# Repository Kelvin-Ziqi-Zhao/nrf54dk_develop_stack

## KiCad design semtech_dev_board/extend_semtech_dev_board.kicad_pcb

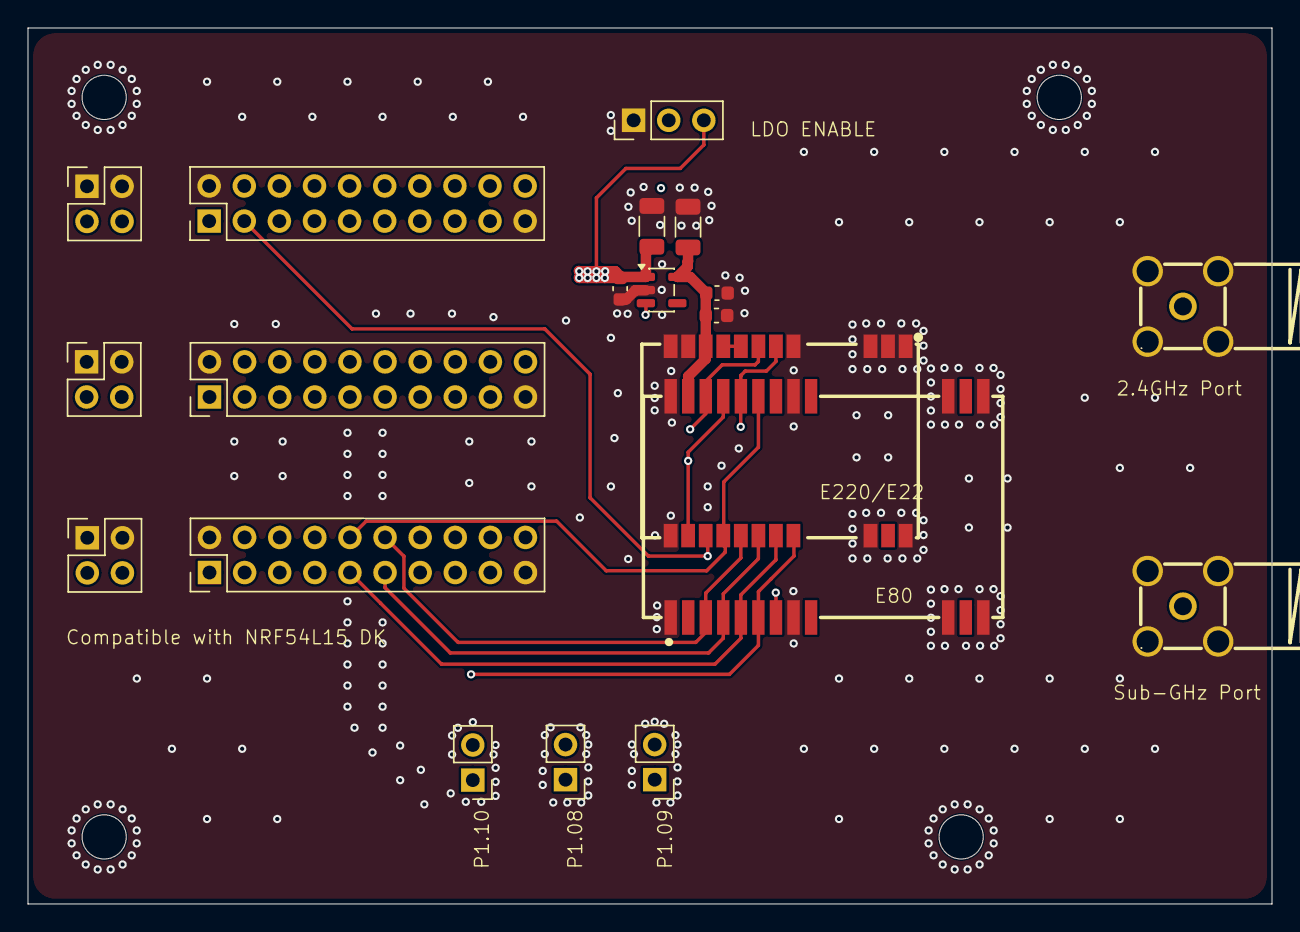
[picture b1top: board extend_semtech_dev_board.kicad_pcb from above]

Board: 4 copper layers, 90.0 x 63.4 mm, 25 parts (0 on the bottom side), 20 nets.

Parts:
C1, C2: 10u; C_1206_3216Metric
C4, C5: 1u; C_0603_1608Metric
C6: 100n; C_0603_1608Metric
H1, H3, H5, H6: MountingHole; MountingHole_3.2mm_M3
J1, J2, J3: Conn_02x02_Odd_Even; PinHeader_2x02_P2.54mm_Vertical
J4, J5, J6: Conn_02x10_Odd_Even; PinHeader_2x10_P2.54mm_Vertical
JP1, JP2, JP3: Jumper_2_Bridged; PinHeader_1x02_P2.54mm_Vertical
JP4: Jumper_3_Bridged12; PinHeader_1x03_P2.54mm_Vertical
RF1, RF2: BWSMA-KWE-Z001; C496551_SMA-TH_BWSMA-KWE-Z001
U1: drawing
U2: E80-900M2212S_C55338904; C55338904_WIRELM-SMD_E80-900M2212S
U3: E220-900M22S; C2971736_WIRELM-SMD_22P-L20_0-W14_0-P1_27-BR
U4: TLV75533PDBV; SOT-23-5

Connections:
+3V3: C2.2, C5.1, C6.1, U2.25 (VCC), U3.9 (VCC), U4.5 (OUT)
+5V: C1.2, C4.1, J1.3, J2.3, J3.3, JP4.3 (B), U4.1 (IN)
/EN: JP4.2 (C), U4.3 (EN)
/HF: RF2.5, U2.12 (ANT)
/LF: RF1.5, U2.15 (ANT), U3.21 (ANT)
/NRST: J6.10, U2.21 (LR_NRESET), U3.15 (NRST)
/P1.08/DIO: JP1.2 (B), U2.23 (DIO8), U3.13 (DIO1)
/P1.09/DIO: JP2.2 (B), U2.22 (DIO9), U3.5 (DIO3)
/P1.10/DIO/RXEN: JP3.2 (B), U2.24 (DIO7), U3.6 (RXEN)
/nrf54l15-dk/P0.00: J4.3, U2.7 (BUSY), U3.14 (BUSY)
/nrf54l15-dk/P1.08: J5.11, JP1.1 (A)
/nrf54l15-dk/P1.09: J5.12, JP2.1 (A)
/nrf54l15-dk/P1.10: J5.13, JP3.1 (A)
/nrf54l15-dk/P2.06: J6.9, U2.5 (SCK), U3.18 (SCK)
/nrf54l15-dk/P2.08: J6.11, U2.4 (MOSI), U3.17 (MOSI)
/nrf54l15-dk/P2.09: J6.12, U2.3 (MISO), U3.16 (MISO)
/nrf54l15-dk/P2.10: J6.13, U2.6 (NSS), U3.19 (NSS)
GND: C1.1, C2.1, C4.2, C5.2, C6.2, J1.1 (GND), J1.2, J2.1, J2.2, J3.1, J3.2, J4.2, J4.19, J5.2, J5.19, J6.2, J6.19, JP4.1 (A), RF1.1, RF1.2, RF1.3, RF1.4, RF2.1, RF2.2, RF2.3, RF2.4, U2.1 (GND), U2.8 (GND), U2.11 (GND), U2.13 (GND), U2.14 (GND), U2.16 (GND), U2.19 (GND), U2.26 (GND), U3.1 (GND), U3.2 (GND), U3.3 (GND), U3.4 (GND), U3.10 (GND), U3.11 (GND), U3.12 (GND), U3.20 (GND), U3.22 (GND), U4.2 (GND)
unnamed: U3.7 (TXEN), U3.8 (DIO2)
VDD: J4.1, J4.20, J5.1, J5.20, J6.1, J6.20

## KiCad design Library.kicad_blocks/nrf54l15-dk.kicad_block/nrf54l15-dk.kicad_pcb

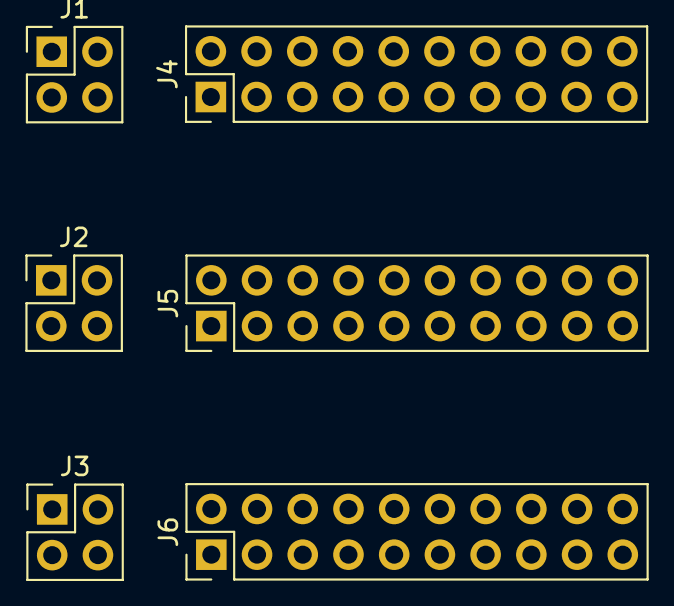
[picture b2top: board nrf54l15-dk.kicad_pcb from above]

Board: 2 copper layers, 13 parts (0 on the bottom side), 3 nets, no tracks yet.

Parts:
H1, H2, H3, H4, H5, H6: MountingHole; MountingHole_3.2mm_M3
J1, J2, J3: Conn_02x02_Odd_Even; PinHeader_2x02_P2.54mm_Vertical
J4, J5, J6: Conn_02x10_Odd_Even; PinHeader_2x10_P2.54mm_Vertical
U1: drawing

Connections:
+5V: J1.3, J2.3, J3.3
GND: J1.1 (GND), J1.2, J2.1, J2.2, J3.1, J3.2, J4.2, J4.19, J5.2, J5.19, J6.2, J6.19
VDD: J4.1, J4.20, J5.1, J5.20, J6.1, J6.20
